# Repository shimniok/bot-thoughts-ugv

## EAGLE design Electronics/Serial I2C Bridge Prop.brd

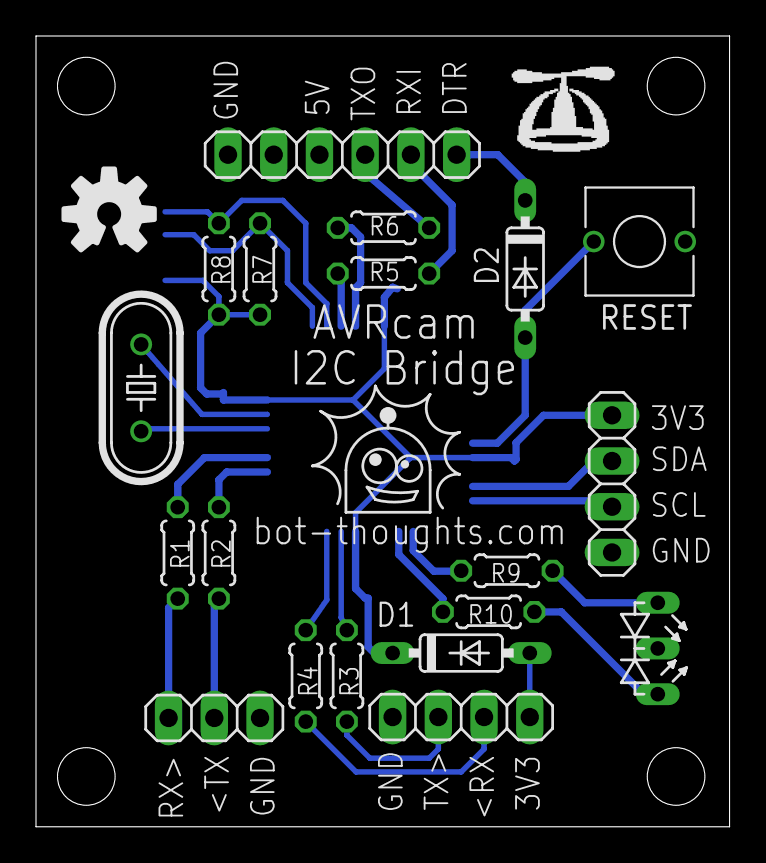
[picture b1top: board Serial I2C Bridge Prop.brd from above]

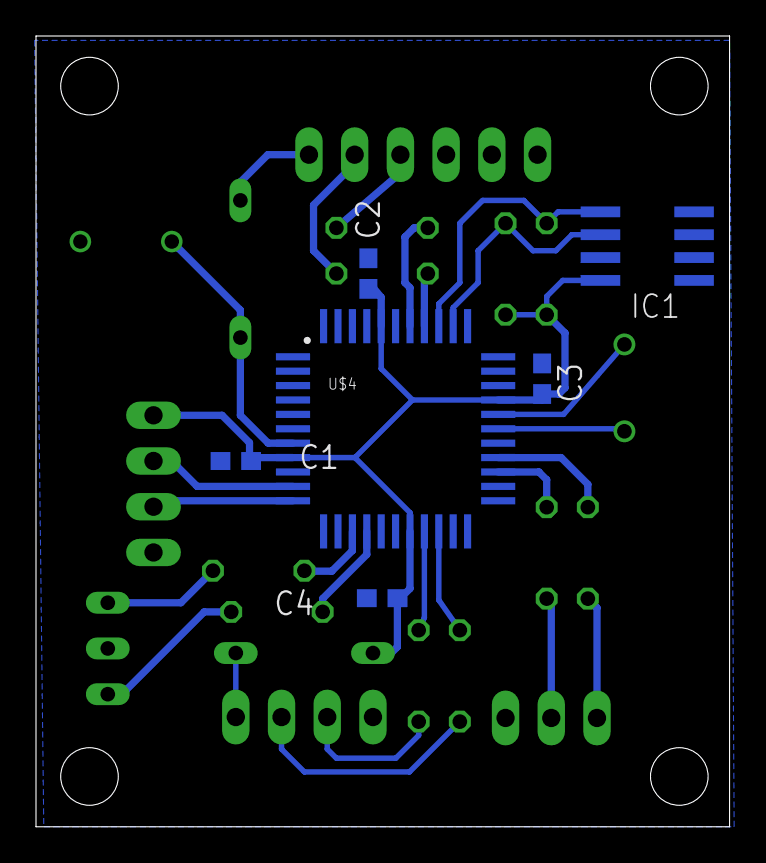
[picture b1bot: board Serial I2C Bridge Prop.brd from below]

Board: 2 copper layers, 38.5 x 43.9 mm, 25 parts (6 on the bottom side), 27 nets.

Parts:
C1, C2, C3, C4: C0603
D1, D2: 1N4148; DO35-7
D3: DUOLED
IC1: 24LC256SN; SO-08
JP1: FTDI; 1X06
JP3: CAM; 1X03
JP4: I2C; 1X04
JP5: DIAG; 1X04
Q1: 5MHz; HC49/S
R1, R2, R3, R4, R5, R6: 1.8K; 0204/5
R7, R8: 10K; 0204/5
R9, R10: 390; 0204/5
S1: RESET; 6MMTACTILE
U$4: P8X32A-Q44

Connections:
3.3V: C1.1, C2.1, C3.1, C4.1, D1.C, IC1.8, JP4.1, R7.2, R8.2, U$4.8, U$4.18, U$4.30, U$4.40
!RESET: D2.A, S1.P$2, U$4.7
<RXI: JP3.1, R1.2
<RXI_D: JP5.2, R4.2
<RXI_D_LV: R4.1, U$4.20
<RXI_LV: R1.1, U$4.26
GND: C1.2, C2.2, C3.2, C4.2, D3.K, IC1.1, IC1.2, IC1.3, IC1.4, IC1.7, JP1.6, JP3.3, JP4.4, JP5.4, S1.P$1, U$4.5, U$4.17, U$4.27, U$4.39
LED1: R9.1, U$4.14
LED2: R10.2, U$4.15
unnamed: D2.C, JP1.1
unnamed: Q1.2, U$4.28
unnamed: D1.A, JP5.1
unnamed: Q1.1, U$4.29
unnamed: JP1.2, R5.2
unnamed: JP1.3, R6.2
unnamed: D3.A1, R9.2
unnamed: D3.A2, R10.1
P28: IC1.6, R7.1, U$4.35
P29: IC1.5, R8.1, U$4.36
P30: R5.1, U$4.37
P31: R6.1, U$4.38
SCL: JP4.3, U$4.11
SDA: JP4.2, U$4.10
TXO>: JP3.2, R2.2
TXO_D>: JP5.3, R3.2
TXO_D_LV: R3.1, U$4.19
TXO_LV>: R2.1, U$4.25

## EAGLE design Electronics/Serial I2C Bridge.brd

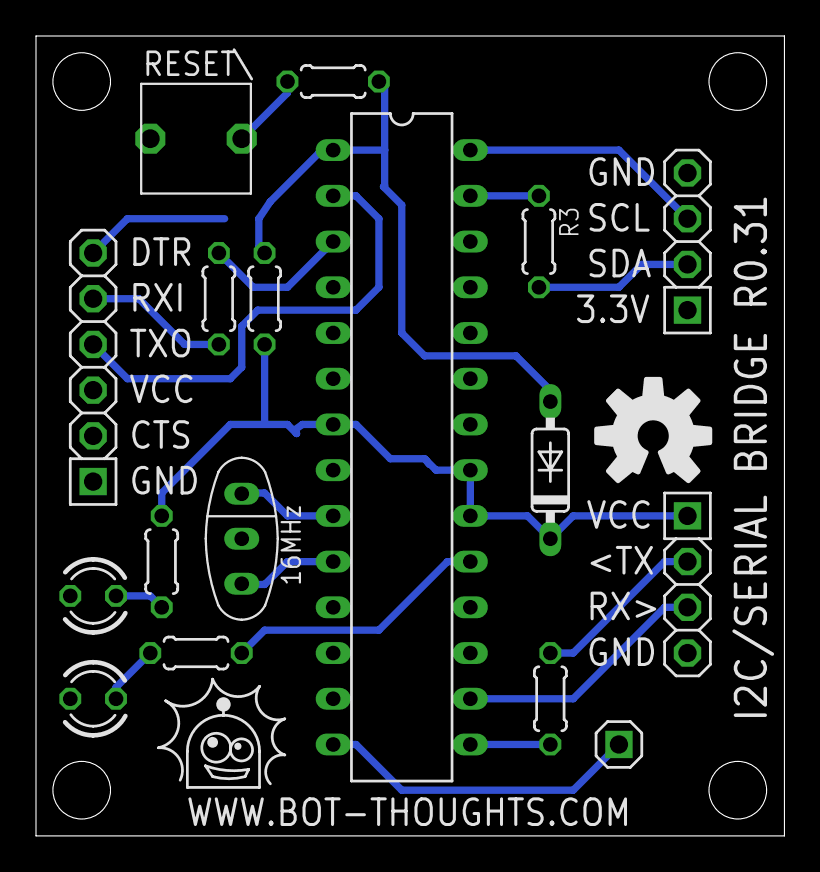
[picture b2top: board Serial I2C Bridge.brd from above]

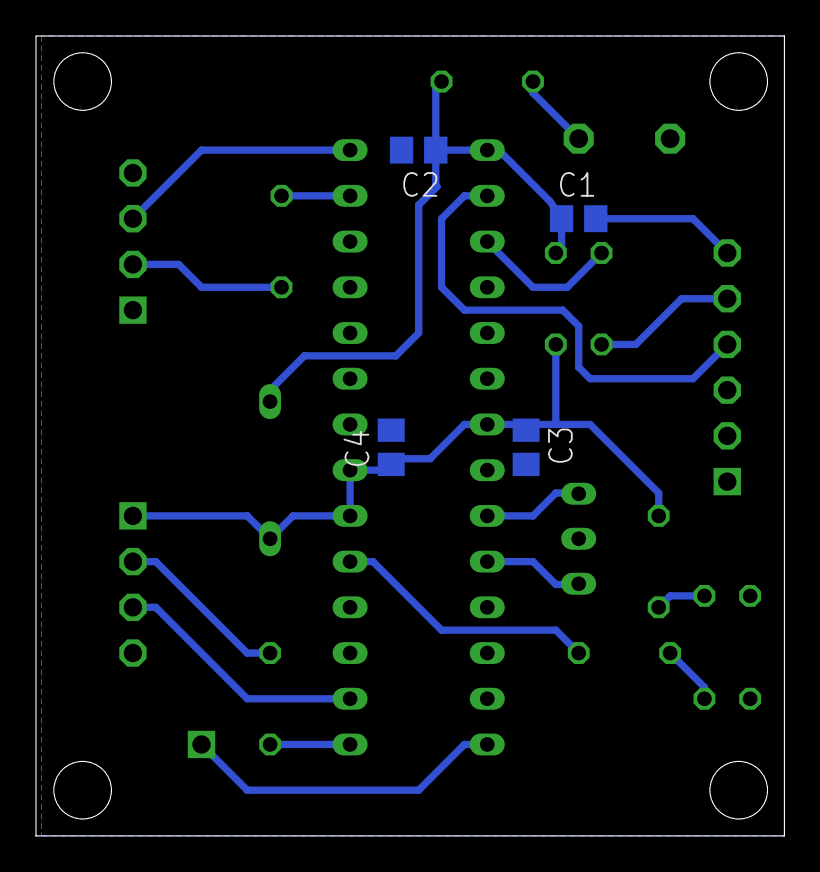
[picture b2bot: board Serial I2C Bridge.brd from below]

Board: 2 copper layers, 41.6 x 44.4 mm, 21 parts (4 on the bottom side), 20 nets.

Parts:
C1, C2, C3, C4: 0.1uF; C0805
D2: 1N4148; DO35-7
IC1: ATmega328P; DIL28-3
JP1: I2C; 1X04-S
JP2: CAM; 1X04-S
JP3: RDY; 1X01-S
JP4: FTDI; 1X06-S
LED1, LED2: STAT1; LED3MM
Q1: 16MHz; CSTLS_G9
R1, R3, R4, R6: 1K; 0204/5
R2, R5, R7: 330; 0204/5
S1: RESET\; EVQ11X09

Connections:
5V: C3.1, C4.1, D2.C, IC1.7, IC1.20, IC1.21, JP2.1, R1.2, R7.1
<RX: IC1.16, JP2.3
<RXD/TXO: IC1.2, JP4.4
DTR: C1.2, JP4.6
GND: C2.2, C3.2, C4.2, IC1.8, IC1.22, JP1.4, JP2.4, JP4.1, LED1.K, LED2.K, Q1.2, S1.1
LV_SDA: JP1.2, R3.2
LV_TX>: JP2.2, R4.2
LV_TXD/RXI>: JP4.5, R6.2
unnamed: IC1.9, Q1.1
unnamed: IC1.10, Q1.3
unnamed: LED1.A, R2.2
unnamed: IC1.19, R2.1
unnamed: C1.1, C2.1, D2.A, IC1.1, R1.1, R5.1
unnamed: R5.2, S1.2
unnamed: LED2.A, R7.2
READY: IC1.14, JP3.1
RXI/TXD>: IC1.3, R6.1
SCL: IC1.28, JP1.3
SDA: IC1.27, R3.1
TX>: IC1.15, R4.1

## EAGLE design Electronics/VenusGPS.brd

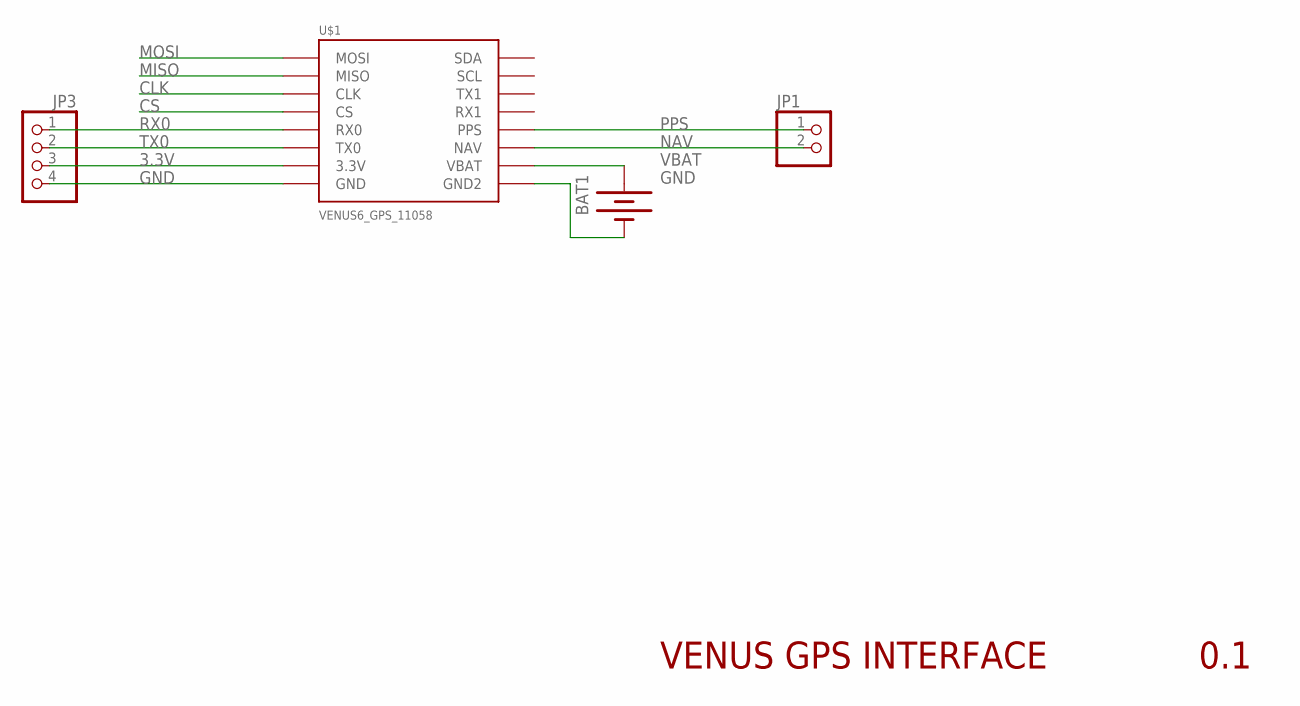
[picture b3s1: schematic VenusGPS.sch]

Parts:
BAT1: BATTERY12MM; BATTCON_12MM; PARTNO 3000
JP1: PINHD-1X02_2.54; 1X02
JP3: PINHD-1X04_2.54; 1X04
U$1: VENUS6_GPS_11058; VENUS6

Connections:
3.3V: JP3.3, U$1.P7 (3.3V)
CLK: U$1.P3 (CLK)
CS: U$1.P4 (CS)
GND: BAT1.GND (-), JP3.4, U$1.P8 (GND), U$1.P9 (GND2)
MISO: U$1.P2 (MISO)
MOSI: U$1.P1 (MOSI)
NAV: JP1.2, U$1.P11 (NAV)
PPS: JP1.1, U$1.P12 (PPS)
RX0: JP3.1, U$1.P5 (RX0)
TX0: JP3.2, U$1.P6 (TX0)
VBAT: BAT1.PWR@1 (+), U$1.P10 (VBAT)

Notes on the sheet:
VENUS GPS INTERFACE
0.1

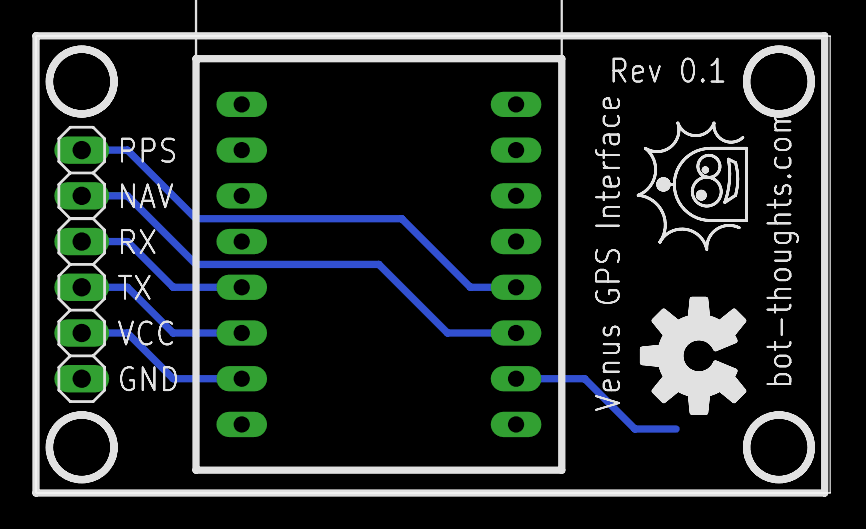
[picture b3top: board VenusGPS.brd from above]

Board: 2 copper layers, 44.1 x 25.4 mm, 4 parts (1 on the bottom side), 7 nets.

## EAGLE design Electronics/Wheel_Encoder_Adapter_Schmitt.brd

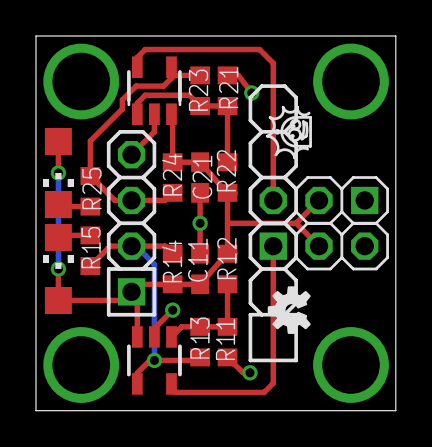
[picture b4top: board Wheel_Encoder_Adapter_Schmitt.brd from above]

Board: 2 copper layers, 20.0 x 20.8 mm, 19 parts (0 on the bottom side), 10 nets.

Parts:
C11, C21: 1uF; C0603
IC1, IC2: TL331; DBV-R-PDSO-G5
JP1: RIGHT; 1X03-S
JP2: LEFT; 1X03-S
JP3: TO MCU; 1X04-S
LED1: LEFT; CHIPLED_1206
LED2: RIGHT; CHIPLED_1206
R11, R21: 12K; R0603
R12, R22: 56K; R0603
R13, R23: 51K; R0603
R14, R24: 10K; R0603
R15, R25: 330; R0603

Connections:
GND: C11.2, C21.2, IC1.2, IC2.2, JP1.1, JP2.3, JP3.4, R11.1, R21.1
IN_LEFT: IC1.5, JP2.1
IN_RIGHT: IC2.5, JP1.3
unnamed: LED1.C, R15.1
unnamed: IC1.1, R11.2, R12.1, R13.1
unnamed: LED2.C, R25.1
unnamed: IC2.1, R21.2, R22.1, R23.1
OUT_LEFT: IC1.4, JP3.2, R13.2, R14.1, R15.2
OUT_RIGHT: IC2.4, JP3.3, R23.2, R24.1, R25.2
VCC: C11.1, C21.1, IC1.3, IC2.3, JP1.2, JP2.2, JP3.1, LED1.A, LED2.A, R12.2, R14.2, R22.2, R24.2

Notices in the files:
parts and their libraries:
SparkFun: Licensing: CC v3.0 Share-Alike You are welcome to use this library for commercial purposes.
